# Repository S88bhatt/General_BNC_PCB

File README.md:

# General_BNC_PCB
General PCB which contains 6 BNCs, and will be used for a variety of different circuits to supply input and produce output.

## Use
This board is a very simple board, meant to be used for many different circuits. Essentially, the value of this circuit is to have a single standard board of BNC's for future use.

## Images
Images will be uploaded later to demonstrate examples of when this board is used, and how it was used

## FreeCAD
There is not a fixed FreeCAD design for this board since it depends on how many an individual circuit may use, however, a FreeCAD design meant for this board will be uploaded soon as a reference as to how it can be made

## Gimp
There will not be a Gimp file for this since it will have different labels for different circuits, however, a generic Gimp file will be uploaded so that the title for each BMC can be changed, but the location of the title is already verified.

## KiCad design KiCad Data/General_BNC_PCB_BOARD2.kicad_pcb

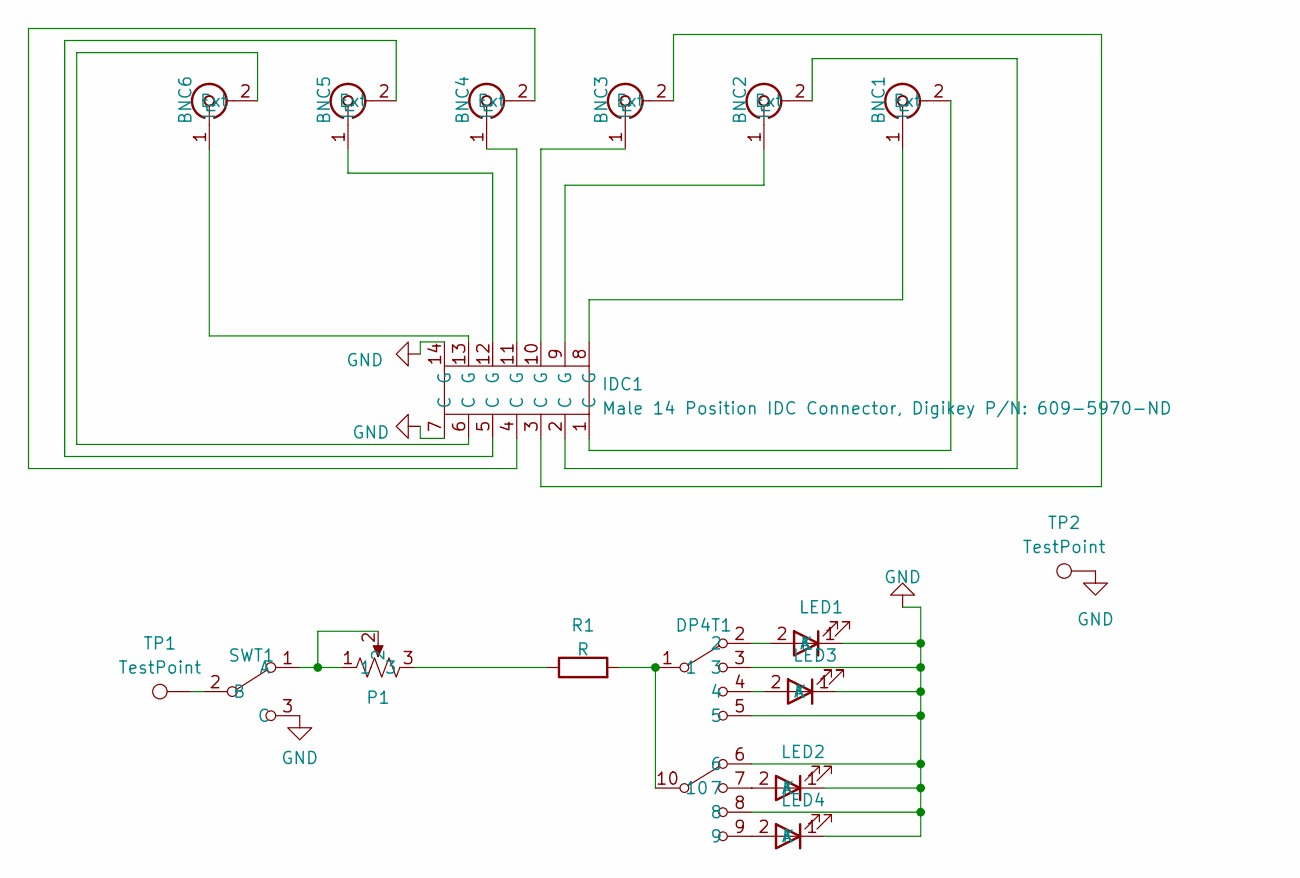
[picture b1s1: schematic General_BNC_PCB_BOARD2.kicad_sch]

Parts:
BNC1, BNC2, BNC3, BNC4, BNC5, BNC6: Coaxial Connectors RA, Digikey P/N: WM5514-ND; Right Angle Single Level BNC
DP4T1: Rotary Switches 2 POLE 4 POS D SHAFT, Mouser P/N: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; Rotary Switches 2 Pole 4 Position
IDC1: Male 14 Position IDC Connector, Digikey P/N: 609-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; Male IDC Connector
LED1, LED2, LED3, LED4: LED Mouser P/N: 551-0407F; LED
P1: Potentiometer, Digikey P/N: 3590P-2-103L-ND; Potentiometer
R1: R; R_Axial_DIN0207_L6.3mm_D2.5mm_P10.16mm_Horizontal
SWT1: AV2 SPDT Switch, Digikey P/N: CKN1447-ND; AV2_Switch
TP1, TP2: TestPoint

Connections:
GND: DP4T1.3, DP4T1.5, DP4T1.6, DP4T1.8, IDC1.7 (C), IDC1.14 (G), LED1.1 (K), LED2.1 (K), LED3.1 (K), LED4.1 (K), SWT1.3 (C), TP2.1
unnamed: BNC1.2 (Ext), IDC1.1 (C)
unnamed: BNC1.1 (In), IDC1.8 (G)
unnamed: BNC2.2 (Ext), IDC1.2 (C)
unnamed: BNC2.1 (In), IDC1.9 (G)
unnamed: BNC3.2 (Ext), IDC1.3 (C)
unnamed: BNC3.1 (In), IDC1.10 (G)
unnamed: BNC4.2 (Ext), IDC1.4 (C)
unnamed: BNC4.1 (In), IDC1.11 (G)
unnamed: BNC5.2 (Ext), IDC1.5 (C)
unnamed: BNC5.1 (In), IDC1.12 (G)
unnamed: BNC6.2 (Ext), IDC1.6 (C)
unnamed: BNC6.1 (In), IDC1.13 (G)
unnamed: DP4T1.1, DP4T1.10, R1.2
unnamed: DP4T1.2, LED1.2 (A)
unnamed: DP4T1.7, LED2.2 (A)
unnamed: DP4T1.4, LED3.2 (A)
unnamed: DP4T1.9, LED4.2 (A)
unnamed: P1.3, R1.1
unnamed: P1.1, P1.2, SWT1.1 (A)
unnamed: SWT1.2 (B), TP1.1

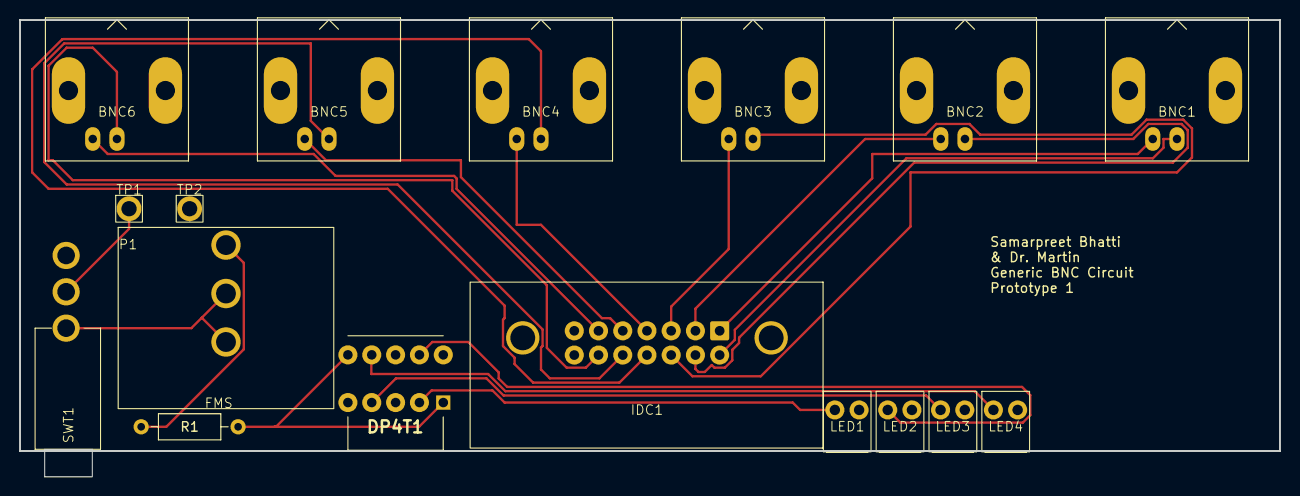
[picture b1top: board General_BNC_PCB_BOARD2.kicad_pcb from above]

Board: 2 copper layers, 132.1 x 47.9 mm, 17 parts (0 on the bottom side), 21 nets.

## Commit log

2023-07-20 Create Read
2023-07-26 Updated STL file
2023-07-26 Updated STL, has not resistor now
2023-08-24 Updated distance to edge of PCB for BNC's
2023-09-06 Updated board
